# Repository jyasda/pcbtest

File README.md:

Developed a custom pcb to measure temperature using DHT11, rhombus themed

.

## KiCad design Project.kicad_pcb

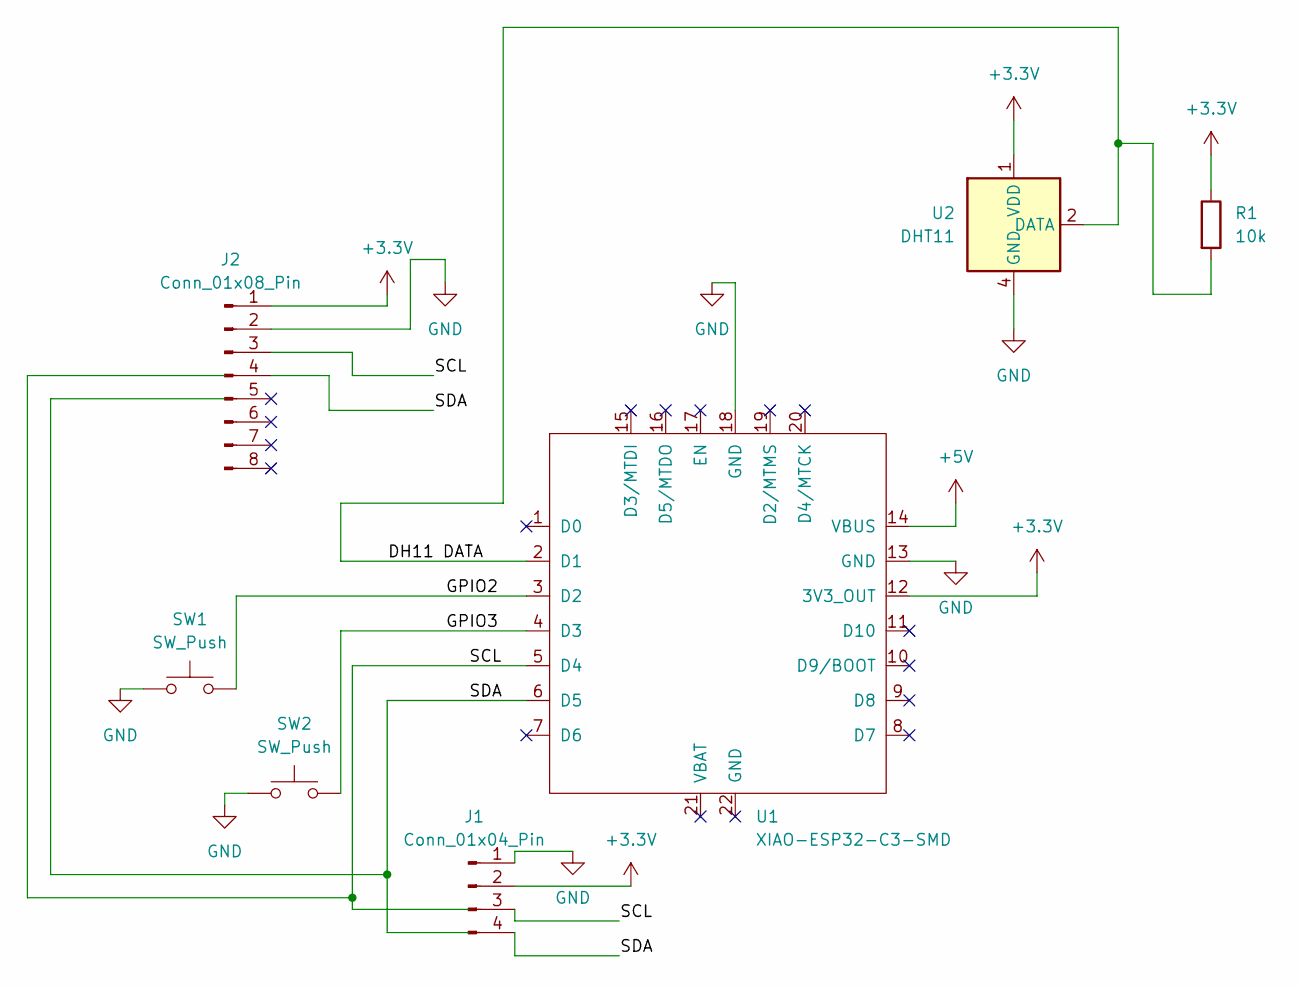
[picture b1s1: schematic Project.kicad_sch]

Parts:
J1: Conn_01x04_Pin; Display_128x64_096_I2C
J2: Conn_01x08_Pin; PinHeader_1x08_P2.54mm_Vertical
R1: 10k; R_Axial_DIN0204_L3.6mm_D1.6mm_P7.62mm_Horizontal
SW1, SW2: SW_Push; SW_Cherry_MX_1.00u_PCB
U1: XIAO-ESP32-C3-SMD
U2: DHT11; Aosong_DHT11_5.5x12.0_P2.54mm

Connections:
+3.3V: J1.2, J2.1, R1.1, U1.12 (3V3_OUT), U2.1 (VDD)
+5V: U1.14 (VBUS)
/DH11 DATA: R1.2, U1.2 (D1), U2.2 (DATA)
/GPIO2: SW1.2, U1.3 (D2)
/GPIO3: SW2.2, U1.4 (D3)
/SCL: J1.3, J2.3, U1.5 (D4)
/SDA: J1.4, J2.4, U1.6 (D5)
GND: J1.1, J2.2, SW1.1, SW2.1, U1.13 (GND), U1.18 (GND), U2.4 (GND)

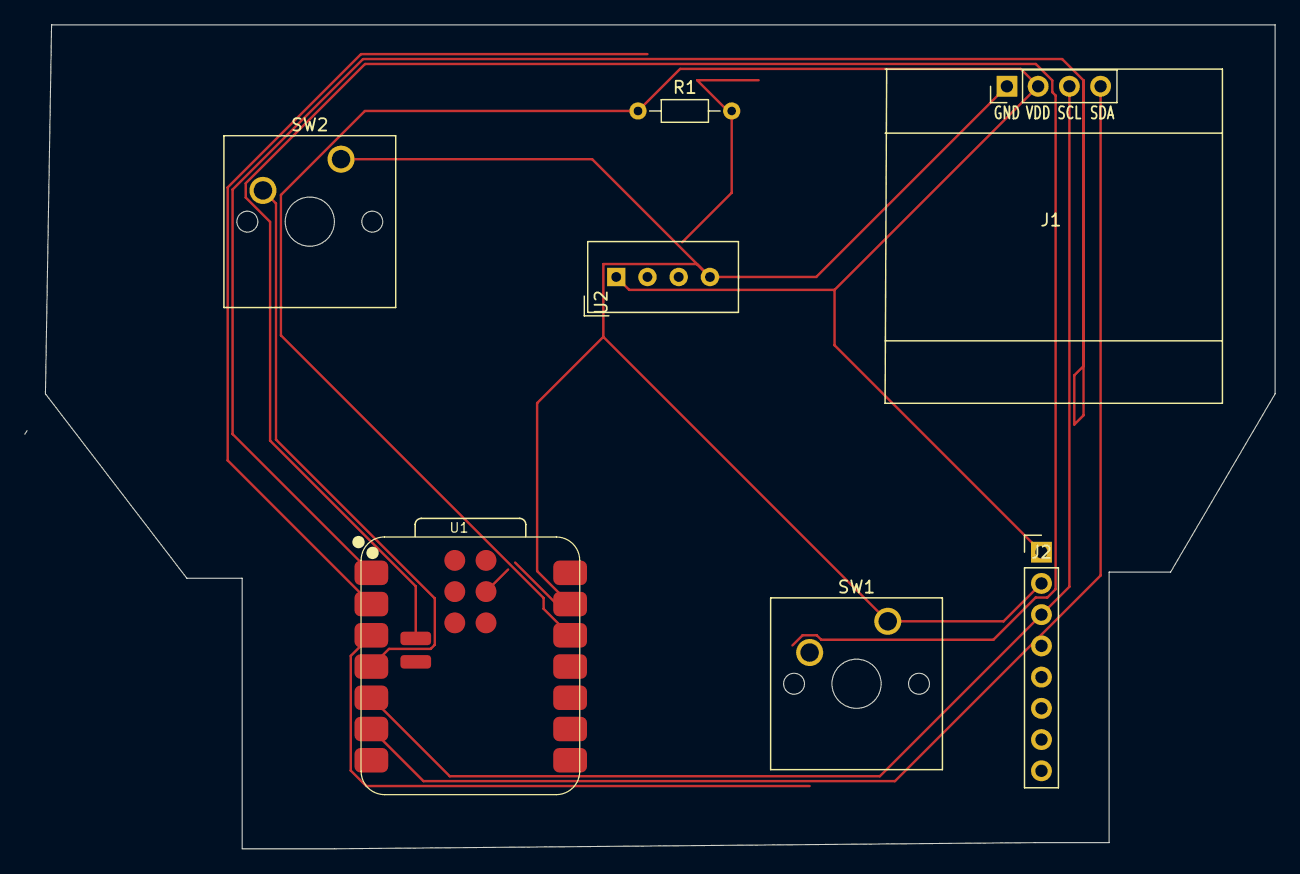
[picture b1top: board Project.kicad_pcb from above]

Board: 2 copper layers, 101.7 x 67.0 mm, 7 parts (0 on the bottom side), 7 nets.
